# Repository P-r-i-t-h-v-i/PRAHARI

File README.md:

# PRAHARI

Wearable health/safety monitoring band built on Seeed XIAO nRF52840, with LoRa (SX1278/Ra-02/HW-691), MAX30100 heart rate sensor, and MLX90614/AHT20 temperature sensing.

## Hardware

### SX1278 / Ra-02 / HW-691 LoRa Module → XIAO nRF52840
- VCC: 3V3
- GND: GND
- MOSI: D10
- MISO: D9
- SCK: D8
- NSS (CS): D3
- RESET (RST): D2
- DIO0: D1

### MAX30100 Heart Rate Sensor → XIAO nRF52840
- VIN: 3V3
- GND: GND
- SCL: D5
- SDA: D4
- INT: D0 (optional)

### MLX90614 / AHT20 Temperature Sensor(s) → XIAO nRF52840
- VIN/VCC: 3V3
- GND: GND
- SCL: D5
- SDA: D4

### SSD1306 OLED Display → XIAO nRF52840
- VCC: 3V3
- GND: GND
- SDA: D4 (shared I2C bus)
- SCL: D5 (shared I2C bus)

### Shared pins
- **3V3**: shared power rail for all modules. XIAO nRF52840 is not 5V tolerant — do not use a 5V rail.
- **GND**: common star ground for all modules to reduce PPG signal noise.
- **D4 (SDA) / D5 (SCL)**: shared I2C bus. MAX30100, MLX90614, AHT20, and the OLED can all coexist here since each uses a distinct I2C address.

## Structure
- `firmware/oled_test/` — standalone SSD1306 OLED test sketch (Adafruit_GFX + Adafruit_SSD1306)
- `firmware/max30100_test/` — heart rate/SpO2 test sketch (SparkFun MAX3010x library)
- `firmware/i2c_scanner/` — I2C bus scanner, useful for diagnosing wiring/address issues
- `firmware/max30100_probe/` — raw I2C register probe that reads the sensor's PART_ID (0xFF) to identify the actual chip
- `firmware/lora_test/` — SX1278 LoRa test sketch (LoRa library by Sandeep Mistry), currently unresolved: chip not responding over SPI (see Known issues)
- `firmware/lora_probe/` — raw SPI register probe that reads the SX1278's RegVersion (0x42) directly, bypassing the LoRa library
- `firmware/heart_rate_oled/` — combined sketch: reads live heart rate and displays BPM on the SSD1306 OLED
- `pcb/` — KiCad PCB project for the PRAHARI board (schematic, layout, footprints, gerbers, BOM in `pcb/out/`)

## Known hardware note
The "MAX30100" heart-rate breakout in this build actually reports PART_ID `0x15` (MAX30102/MAX30105), not the true MAX30100 (`0x11`) — a common mislabeling on cheap breakout boards. Confirmed via `firmware/max30100_probe`. As a result, `firmware/max30100_test` uses the **SparkFun MAX3010x Pulse and Proximity Sensor Library** (MAX30105 API), not `MAX30100lib`, which fails to initialize against this chip regardless of I2C clock speed.

## Known issues
- LoRa module (SX1278/Ra-02/HW-691) not responding over SPI: `RegVersion` (0x42) reads `0x00` regardless of SPI clock speed (tried 1MHz and 100kHz), and after multiple wiring re-checks (VCC, MISO, GND, MOSI, SCK, NSS, RESET). Frequency (433MHz) and pin mapping have been verified correct in code/source. Suspect either a persistent physical connection fault or a dead module — next step is a multimeter continuity check per-wire, or swapping in a spare module if available.

## Recent changes
- **2026-08-30** — Added standalone SSD1306 OLED test sketch (`firmware/oled_test/oled_test.ino`); flashed and verified on XIAO nRF52840 hardware.
- **2026-08-30** — Added standalone MAX30100 heart rate/SpO2 test sketch (`firmware/max30100_test/max30100_test.ino`); flashed and verified on XIAO nRF52840 hardware.
- **2026-08-30** — Added `firmware/i2c_scanner` and `firmware/max30100_probe` diagnostics; discovered the heart-rate breakout is actually a MAX30102/MAX30105 (PART_ID 0x15) mislabeled as MAX30100; switched `max30100_test` to the SparkFun MAX3010x library, confirmed working (live IR readings on hardware).
- **2026-08-30** — Verified `max30100_test` end-to-end with a live finger on the sensor: IR rose from ~400 (no finger) to ~96000, avg BPM stabilized at 78.
- **2026-08-30** — Added `firmware/lora_test` and `firmware/lora_probe`; LoRa module not yet responding over SPI, diagnosis in progress (see Known issues).
- **2026-08-30** — Added `firmware/heart_rate_oled`, combining the heart-rate sensor with the SSD1306 OLED to display live BPM; flashed and both devices initialized successfully.
- **2026-08-30** — Fixed `heart_rate_oled` showing unrealistically low BPM (e.g. 8) right after placing a finger: the rolling average was dividing by the fixed window size (4) even before 4 real beats were recorded, diluting early readings with zero-initialized buffer slots. Now averages only over beats actually recorded, and resets the average when the finger is removed so a fresh placement doesn't inherit a stale reading.
- **2026-08-30** — Added serial debug logging to `heart_rate_oled` (beat delta/BPM, rejection reason, IR/finger/avg snapshot every 1s); compiled and uploaded to XIAO nRF52840 hardware via arduino-cli (installed `adafruit-nrfutil` locally to enable DFU upload over `/dev/ttyACM0`).
- **2026-09-01** — Added `pcb/` — KiCad PCB project for the PRAHARI board (schematic, layout, footprints, gerbers, BOM).
- **2026-09-01** — Documented repo/Obsidian sync policy in CLAUDE.md: this folder always pushes to `P-r-i-t-h-v-i/PRAHARI` and syncs `Projects/PRAHARI.md` in Obsidian automatically on every change, no confirmation needed.
- **2026-09-02** — Imported rev B PCB from `PRAHARI-PCB.zip` into `pcb/` (replacing rev A files; leftover rev A gerbers/drills in `pcb/out/` root are untracked and pending removal); verified all 38 footprints match schematic, netlist and KiCad 10 libraries pad-for-pad; ran ERC/DRC with kicad-cli 10.0.6 (flatpak): ERC clean (202 known cosmetic warnings), DRC fails the project bar — 3 errors (J6/U2 courtyard collision, RF clearance) + 4 unconnected (LORA_DIO1, DW_VDD ×2, F/B GND pour tie) vs expected 0/0/8; last DRC-clean board is the nested `PRAHARI-revB-verified-20260902-1120.zip`; added `.gitignore` for nested zips, backups and lock files.
- **2026-09-25** — Added `pcb/scripts/build_report_pdf.py` PDF report generator (title/idea, how-it-works, PCB renders, schematic, BOM, build status); iteratively cleaned it to remove PS number/category, the duplicate bottom-PCB image, all "SIH 2026" references (page header and schematic company field), the "open issues" section, and the "things to reconcile" section; added a final "From Prototype to Integrated Board" section answering the prototype-evolution, improvement, and testing-insight/next-steps questions in full prose.
- **2026-09-25** — Removed "rev B hardware" from the PDF report's page footer (was repeated on every page).

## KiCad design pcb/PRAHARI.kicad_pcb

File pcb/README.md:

# PRAHARI — carrier board, rev B

Prototype carrier PCB for **PRAHARI, The Countdown Band** (Point Break, SIH 2026, PS 26181).

**70 × 40 mm, 2 layer, 1.6 mm FR4.** Every active part is still an off-the-shelf
module on a 2.54 mm header. rev B upgrades the sensing, radio and power chain;
the board outline, mounting holes and connector positions are unchanged.

| | |
|---|---|
| Board | 70 × 40 mm, 2 mm corner radius, 4 × M2 mounting holes |
| Stackup | 2 layer, 1.6 mm, 1 oz, GND pour both sides |
| Parts | 38 footprints, 22 BOM line items |
| Routing | 345 tracks / 772 mm, 156 vias (23 routing + 133 ground stitching) |
| Widths | 0.25 mm signal, 0.6 mm power, 0.9 mm RF |
| Pads | 75 SMD, 39 plated through |
| Process | 0.25 mm track / 0.2 mm space / 0.3 mm drill — cheapest JLCPCB & PCBWay tier |
| DRC | **0 violations, 0 unconnected** — 8 cosmetic parity warnings |
| ERC | 202 warnings: 195 off-grid (pre-existing, see *Known warnings*) + 7 deliberate |

---

## What changed from rev A

| | rev A | rev B | Why |
|---|---|---|---|
| PPG | MAX30100 | **MAX30102** | Glass shield, ambient-light cancellation, and 3V3 bus levels — which retires rev A's "1.8 V pull-ups fighting R1/R2" warning entirely |
| Skin temp | MLX90614 (IR) | **MAX30208** (contact) | The thermopile had to see skin across an air gap that wrist curvature keeps changing. A contact digital sensor does not care: ±0.1 °C over I²C |
| Ambient | AHT20 | AHT20 | Unchanged — still the WBGT wet-bulb input |
| Radio | Ra-02 (SX1278) | **Ra-01SH (SX1262)** | 4.2 mA RX vs 11 mA, built-in DC-DC, +22 dBm. **Changes band — see below** |
| Display | 0.96" SSD1306 | **0.91" SSD1306** | Same driver and same 0x3C address, smaller panel, lower peak charge-pump current (<15 mA) |
| Battery | bare LiPo | **DW01A + FS8205A** | On-carrier over-charge / over-discharge / over-current protection |
| Actuator | 1027 ERM + 2N7002 | unchanged | Already correct in rev A |
| MCU | XIAO nRF52840 Sense | unchanged | Already correct in rev A; its BQ25101 is still the only charger |

### ⚠ The radio swap changes the band

The Ra-01SH is an SX1262 part covering **803–930 MHz**. It does *not* cover
433 MHz like the Ra-02 it replaces. Consequences:

- **The whip on J6 drops from 173 mm to 86 mm** (λ/4 at 868 MHz). On a wrist-worn
  band that is a real win — 173 mm of wire was always awkward.
- **In India, keep the radio inside the de-licensed 865–867 MHz sub-band.**
- The deck's "433 MHz mesh" line needs updating to 868 MHz.

If you must stay on 433 MHz, the drop-in is the **Ra-01S / Ra-01SC (SX1268,
410–525 MHz)** — same SPI interface, same BUSY pin, same footprint family. Only
`RA01SH_PINS` and the silkscreen would change. The other option you floated,
the EBYTE E22-400T22S, holds 433 MHz but is a **TTL-UART** module needing
M0/M1/AUX instead of SPI, so it is not a drop-in at all.

---

## What's on it

```
 ANT ▫▫ GND      C3  C1      PRAHARI rev B
 ┌──────────────┐              ┌──────────────────┐
 │  U2 Ra-01SH  │       C2     │ U1  XIAO         │ USB-C
 │  SX1262      │   TP BAT±    │ nRF52840 Sense   │
 │  868 MHz     │   TP 3V3 GND │                  │
 │ U4 C7 R6 U5  │   TP SDA SCL └──────────────────┘
 └──────────────┘
 ┌──────┐ ┌────┐ ┌────┐ ┌────┐            ┌──────┐
 │  J1  │ │ J2 │ │ J3 │ │ J7 │            │  U3  │
 │MAX301│ │MAX │ │AHT │ │OLED│            │ATECC │
 │  02  │ │30208││ 20 │ │0.91│            │ 608A │
 └──────┘ └────┘ └────┘ └────┘            └──────┘
  [J4 BAT]  [J5 MOTOR]  Q1 D1 D2 R3 R4 R5  C4 C5
```

| Ref | Part | Role |
|---|---|---|
| **U1** | Seeed XIAO nRF52840 Sense | MCU, BLE, IMU + mic, BQ25101 LiPo charger |
| **U2** | Ai-Thinker Ra-01SH (SX1262) | LoRa 868 MHz, band-to-band mesh |
| **U3** | ATECC608A-SSHDA (SOIC-8) | Secure element for the anonymised uplink |
| **U4** | DW01A (SOT-23-6) | Li-ion protection: 4.3 V over-charge, 2.4 V over-discharge |
| **U5** | FS8205A (SOT-23-6) | Dual common-drain N-MOSFET — the protection switch pair |
| **J1** | MAX30102 breakout, 1×7 | Red/IR PPG — heart rate, IMU-gated |
| **J2** | MAX30208 breakout, 1×4 | Contact skin temperature, ±0.1 °C |
| **J3** | AHT20 breakout, 1×4 | Air temperature + RH — the WBGT inputs |
| **J7** | 1×4 header | I²C port — 0.91" SSD1306 OLED, or spare |
| **J4** | JST-PH 2 | LiPo in (bare cell — protection is on-board) |
| **J5** | JST-PH 2 | 1027 ERM coin vibration motor |
| **J6** | 2 solder pads | 868 MHz whip + counterpoise |

## GPIO budget

Still exactly 11 GPIO, still all 11 used. The SX1262 has no DIO0 and adds a
**mandatory BUSY**, so D1 changes role and the budget balances unchanged:

| Pin | Net | | Pin | Net |
|---|---|---|---|---|
| D0 | LORA_DIO1 | | D6 | HAPTIC_PWM |
| D1 | **LORA_BUSY** *(was LORA_DIO0)* | | D7 | PPG_INT |
| D2 | LORA_RST | | D8 | SPI_SCK |
| D3 | LORA_NSS | | D9 | SPI_MISO |
| D4 | SDA | | D10 | SPI_MOSI |
| D5 | SCL | | | |

Battery voltage still needs no external divider — the XIAO reads VBAT internally
on P0.31, gated by P0.14, and neither pin reaches the 2×7 header.

A display still costs no GPIO: I²C is a bus, so the SSD1306 hangs off the same
D4/D5 pair as the sensors.

**A Sharp Memory LCD is not possible on this board.** It is an SPI part needing
its own chip-select plus EXTCOMIN, and there is no GPIO left. It only becomes
an option if you move the radio to a UART module and free up SPI.

## I²C bus

| Device | Address |
|---|---|
| AHT20 | 0x38 |
| SSD1306 OLED | 0x3C (0x3D if you move the SA0 jumper) |
| MAX30208 | 0x50 |
| MAX30102 | 0x57 |
| ATECC608A | 0x60 |

Five distinct addresses, no clash. R1/R2 (4k7, on the back) pull up SDA/SCL.
Most breakouts carry their own 4.7 k pull-ups too; with four or five modules
plugged in the bus has plenty, and you can leave R1/R2 unpopulated. Five modules
on flying leads also push bus capacitance toward the 400 pF Fast-mode ceiling —
if the bus is flaky, drop to 100 kHz.

---

## Battery protection (new in rev B)

Standard low-side PCM. The cell's **negative** leg runs through two series FETs
before it becomes system ground, which is why J4 pin 2 is no longer GND:

```
cell+ ──► J4.1 ──► VBAT ──► TP1 ──wire──► XIAO BAT+     (and DW01A VCC via R6)
cell- ──► J4.2 ──► BAT_NEG ──► U5 S1 ──[common drain]──► U5 S2 ──► GND
                                DW01A GND on BAT_NEG, CS on GND (pack-)
```

`BAT_NEG` is a separate net and is deliberately kept out of the ground pour.
`GND` on this board means *pack negative* — the drain side of the FET pair.

### Pin mappings used

| Part | Mapping | Source |
|---|---|---|
| DW01A | 1=OD 2=CS 3=OC 4=TD 5=VCC 6=GND | KiCad's curated `Battery_Management:DW01A` |
| FS8205A | 1=S1 2=G1 3=S2 4=G2 5=D2 6=D1 | KiCad's `Transistor_FET:Q_Dual_NMOS_S1G1S2G2D2D1` |

Note that several secondary web sources give the DW01A as
`1=OC 2=OD 3=CS 4=VSS 5=VDD 6=NC`. That cannot be right — a real DW01A has
*both* VCC and GND plus a TD test pin — so the KiCad mapping is what the board
and the schematic are both built against. Worth one datasheet glance anyway.

### This is redundant with a protected cell

Most 3.7 V 350 mAh wearable cells ship with a DW01A + 8205A PCM already welded
to the tab. Two protections in series is harmless — about 50 mΩ total — but it
is redundant. It is on the carrier because bare cells are rev B's stated
assumption. If you source protected packs, leave U4, U5, R6 and C7 unpopulated
and fit a wire link from J4.2 to the nearest GND pad.

### Charge rate

The 0.5C = 175 mA figure needs checking against the XIAO, not against this
board. The XIAO's on-module BQ25101 sets its charge current with an on-module
resistor and ships configured well below 175 mA. Getting 175 mA means changing
that resistor on the module — the carrier has no charger and cannot influence it.

---

## Before you order — four things to check

**1. Verify the Ra-01SH pad map. This is the biggest open risk on the board.**
The SX1262 *signal set* is certain (NSS, SCK, MOSI, MISO, BUSY, DIO1, NRESET,
VCC, GND, ANT). What is provisional is **which castellated pad each signal sits
on**. The map in `RA01SH_PINS` was chosen to put every signal on the same
physical pad the Ra-02 used, so the routing solution carries over and ANT stays
3.5 mm from J6 — but it is not confirmed against a primary mechanical drawing.
Print `out/gerbers/PRAHARI-F_Cu.gbr` at 1:1, seat a real module on it, and check
before you spend money. If it disagrees, correct that one dict and re-run
`gen_footprints.py` then `gen_pcb.py` — nothing else references pad numbers.

**2. Verify the DW01A OD/OC gate assignment.** `OD(1)` drives `G1` (the FET whose
source sits on B−) and `OC(3)` drives `G2`. That is the usual published
arrangement, but swapping them would make over-discharge protection block
charging instead of discharging. It is a two-line change in the `DW_OD`/`DW_OC`
nets in `design.py`.

**3. The mounting holes are still provisional.** Your `Part1.SLDPRT` /
`Part2.SLDPRT` are the newer proprietary SolidWorks format — not OLE2, not ZIP,
no embedded preview — so the enclosure geometry could not be read. The four M2
holes sit at a symmetric 3.5 mm corner inset. Export the enclosure as **STEP or
DXF** and they can be matched exactly.

**4. Re-price the BOM.** Three parts changed and two were added (U4, U5, R6, C7),
so the deck's ₹3,468 parts total and ₹347-per-worker figure are both stale.

---

---

## Risk register

Ranked by what it costs you if it is wrong. Everything marked *open* needs a
human with the physical part or the enclosure; everything else is closed.

| # | Risk | If wrong | State |
|---|---|---|---|
| 1 | **Ra-01SH pad/signal map** | Board is scrap — every SPI and control line lands on the wrong castellation | **Open.** Mitigated as far as it can be without the part: see below |
| 2 | **DW01A OD/OC gate assignment** | Protection blocks charging instead of discharging — the cell can over-discharge | **Open.** Pin *numbering* is confirmed; only which gate each drives is convention |
| 3 | Mounting holes | Board does not fit the enclosure | **Open.** Needs STEP or DXF — the `.SLDPRT` files cannot be read |
| 4 | Reverse cell insertion on J4 | Reverse voltage reaches the XIAO; the DW01A does **not** protect against this | **Open by design.** J4 is silk-marked `+ −`; check crimp order before first power-up |
| 5 | Protection cluster placement | GND pour stops reaching U4's CS pad — DRC catches it | **Closed.** Guarded by `check_design.py` |
| 6 | `BAT_NEG` track width | Overheating on the cell-negative leg | **Closed.** 0.25 mm / 1 oz ≈ 0.9 A vs ~200 mA peak — about 4× margin |
| 7 | Protection redundant with a protected cell | Nothing — two series FET pairs, ~50 mΩ | **Closed.** DNP path documented above |
| 8 | 195 off-grid ERC warnings hiding a real one | A genuine ERC error goes unnoticed | **Closed.** `check_design.py` triages ERC *by category* and fails on anything that is not off-grid or an isolated label |
| 9 | Stale rev A outputs being uploaded to a fab | Wrong board manufactured | **Closed.** Moved to `out/_revA_archive/`; everything in `out/` is regenerated from the current board |
| 10 | 0.5C = 175 mA charge rate | Slower charging than the deck claims | **Closed as not-our-problem.** It is set by a resistor on the XIAO module, not by this carrier |

### On risk 1 — what is and is not verified

Ai-Thinker publish the Ra-01SH only as image-based or CID-font PDFs, so the pad
table could not be read from a primary source. What *is* established:

- **Signal set — confirmed.** VCC, GND, SCK, MISO, MOSI, NSS, NRESET, BUSY, DIO1,
  ANT (plus optional TXEN/RXEN, which this design leaves unconnected).
  `BUSY` is mandatory on the SX1262 and is wired to D1.
- **Body and package — confirmed** from vendor product data: 17.0 × 16.0 × 3.2 mm,
  dual-row stamp-hole SMD, 16 castellated pads — *identical body to the Ra-02*,
  which is why reusing the rev A pad grid is sound.
- **Which pad carries which signal — NOT confirmed.** This is the open item.

Mitigations already in place:

1. The map lives in exactly one dict, `RA01SH_PINS` in `scripts/design.py`.
   Nothing else in the project references pad numbers — the footprint's pin names
   and the netlist are both derived from it, so they cannot disagree.
2. Every signal sits on the same physical pad the Ra-02 used, so a correction is
   a netlist change, not a re-layout, and ANT stays 3.5 mm from J6.
3. **`out/Ra-01SH-checksheet.svg`** is a 1:1 printable verification sheet.

```bash
python scripts/gen_checksheet.py     # writes out/Ra-01SH-checksheet.svg
```

Open it in a browser, print at **100% / "actual size"** (not "fit to page"),
check the 20 mm ruler on the sheet with a caliper, then seat a real Ra-01SH on
the outline and read off whether pad 8 really is NSS. If it disagrees, fix
`RA01SH_PINS` and re-run `gen_footprints.py` then `gen_pcb.py`.

---

## The guard script

`scripts/check_design.py` re-runs every invariant that was established by hand,
so none of them can regress silently:

```bash
python scripts/check_design.py           # design-level checks, fast
python scripts/check_design.py --full    # + DRC, ERC, and a netlist diff
```

It checks, among other things, that no pad is on two nets, that all 11 XIAO GPIO
are assigned and D1 carries `LORA_BUSY`, that all 16 radio pads are mapped, that
ANT is still on pad 15, that the protection chain is wired as a low-side PCM
pin-for-pin, that `BAT_NEG` is *not* on the Power netclass and *is* in the
router's priority list, and that the protection cluster has not drifted from the
placement that pours cleanly.

With `--full` it also asserts DRC 0/0/8, fails on any ERC category other than
off-grid and isolated labels, and diffs the schematic's own exported netlist
against `design.py` — which is what proves the circuit diagram and the board
still describe the same circuit. **Run it before generating any fab output.**

## Antenna — pick one, not both

The Ra-01SH's ANT pad and the IPEX/U.FL connector on the `-P` variant are the
same RF node.

- **J6 whip (default).** Solder **86 mm** of wire (λ/4 at 868 MHz) to the ANT pad
  and, ideally, another 86 mm to the GND pad as a counterpoise. The RF trace from
  the module to J6 is 3.5 mm of 0.9 mm track over solid ground.
- **IPEX pigtail (better).** Use the Ra-01SH-P, fit a U.FL-to-SMA pigtail, leave
  J6 empty. Zero RF trace.

Do not fit both — a second unterminated path is a stub on the antenna port.
No SMA on the carrier: an edge-launch SMA needs its pads on the board outline (a
real copper-to-edge violation), and a vertical SMA would push the RF trace past
10 mm. Two solder pads 3.5 mm away beat both.

---

## Build and verify

Everything is generated from `scripts/design.py` — components, placement and
netlist live in one file, and **both the schematic and the board are built from
it**, so they cannot drift apart.

```bash
KP="$LOCALAPPDATA/Programs/KiCad/10.0/bin/python.exe"
"$KP" scripts/gen_footprints.py   # XIAO + Ra-01SH (+ Ra-02, kept for rollback)
"$KP" scripts/gen_symbols.py      # XIAO, Ra-01SH, Ra-02, DW01A, FS8205A
"$KP" scripts/gen_project.py      # .kicad_pro, lib tables, design rules
"$KP" scripts/gen_sch.py          # schematic
"$KP" scripts/gen_pcb.py          # place, route, pour, stitch
python scripts/gen_checksheet.py  # 1:1 radio pad-map verification sheet
python scripts/check_design.py --full   # guard: invariants + DRC/ERC + netlist diff
```

**`gen_sch.py` is live again in rev B.** rev A had retired it to protect hand
edits made in eeschema, but a diff showed those edits had not changed the
circuit — same refs, wires, labels and net names — so the schematic is
generated from `design.py` once more. That is what keeps board/schematic parity
at 8 cosmetic warnings while the netlist changes underneath.

`scripts/router.py` is a small two-layer maze router (8-way A* on a 0.1 mm grid,
vias costed at 40 grid units so it prefers to stay on one layer) — KiCad ships
no scriptable autorouter.

To re-check:

```bash
CLI="$LOCALAPPDATA/Programs/KiCad/10.0/bin/kicad-cli.exe"
"$CLI" pcb drc --schematic-parity --severity-all --format json -o out/drc.json PRAHARI.kicad_pcb
"$CLI" sch erc --severity-error --severity-warning --format json -o out/erc.json PRAHARI.kicad_sch
```

Expected: DRC **0 violations, 0 unconnected, 8 parity warnings**; ERC **202
warnings** (195 off-grid + 7 isolated pin labels). Anything else is new.

To rebuild the manufacturing outputs — **use these exact flags.** The CLI
defaults differ from what this project ships and will silently change the file
format if you omit them:

```bash
# BOM - the default --fields drops Description and renames the columns
"$CLI" sch export bom -o out/BOM.csv \
  --fields "Reference,Value,Footprint,Description,QUANTITY" \
  --labels "Reference,Value,Footprint,Description,QUANTITY" \
  --group-by "Value,Footprint" PRAHARI.kicad_sch

# gerbers - without --no-protel-ext you get .gtl/.gbl instead of .gbr
"$CLI" pcb export gerbers -o out/gerbers/ --no-protel-ext \
  --layers "F.Cu,B.Cu,F.Mask,B.Mask,F.Paste,B.Paste,F.Silkscreen,B.Silkscreen,Edge.Cuts" \
  PRAHARI.kicad_pcb

# drills - the flag is --excellon-separate-th, not --separate-files
"$CLI" pcb export drill -o out/gerbers/ --format excellon --excellon-separate-th \
  --generate-map --map-format gerberx2 PRAHARI.kicad_pcb

"$CLI" pcb export pos -o out/positions.csv --format csv --units mm --side both PRAHARI.kicad_pcb
"$CLI" pcb render -o out/top.png --side top --width 1600 --height 1000 --quality high --background opaque PRAHARI.kicad_pcb
```

The gerber zip must contain **14 files**, including `PRAHARI-PTH.drl` and
`PRAHARI-NPTH.drl`. A zip with no `.drl` files is unmanufacturable.

## Manufacturing files

Everything a fab needs is in `out/`:

| File | Use |
|---|---|
| `PRAHARI-gerbers.zip` | upload straight to JLCPCB / PCBWay — 14 files |
| `BOM.csv` | 22 line items, test points and mounting holes excluded |
| `positions.csv` | centroid file, both sides |
| `schematic.pdf` | full schematic |
| `PRAHARI.svg` | same schematic, opens in any browser |
| `netlist.net` | schematic netlist — diff it against `design.py` to prove parity |
| `top.png`, `bottom.png` | 3D renders |
| `drc.json`, `erc.json` | the check reports, regenerated after the last board save |
| `Ra-01SH-checksheet.svg` | **print at 1:1** and verify the radio pad map |
| `_revA_archive/` | superseded rev A renders and zips, kept out of the way |

Order settings: **2 layer, 70 × 40 mm, 1.6 mm, 1 oz, HASL or ENIG.** Nothing on
the board needs better than the default process.

## Assembly order

1. U3 (SOIC-8), U4 and U5 (SOT-23-6), then the 0805/1206 passives — smallest first.
2. Q1 (SOT-23), D1 (SOD-123), D2 (0805 LED).
3. R1, R2 on the **back** side.
4. Headers J1, J2, J3, J7, J6; connectors J4, J5.
5. U2 Ra-01SH — hand-solder the castellations, pin-1 dot at the top left.
6. U1 XIAO last, on a 2×7 header or reflowed onto the castellated lands.
7. Two wires: TP1 → XIAO BAT+, TP2 → XIAO BAT−.

Power up with no battery first and check 3V3 at TP5 before fitting the LiPo.
D2 draws ~1.3 mA continuously — leave it unpopulated for battery-life runs.

## Known warnings

**DRC — 8 schematic parity warnings, cosmetic.** `MOTOR_N`, `ANT` and `HAPTIC_G`
are drawn as bare wires with no net labels, so KiCad auto-names them
`Net-(D1-A)`, `Net-(J6-Pin_1)` and `Net-(Q1-G)` in the schematic while
`design.py` names them explicitly on the board. Same copper, different name. To
clear them, add a net label to each of those three wires.

**ERC — 195 `endpoint_off_grid`, pre-existing.** `gen_sch.py` emits symbol
placements and wire stubs at whole-millimetre offsets rather than snapping to the
1.27 mm connection grid. This is **not new in rev B** — running rev A's
`gen_sch.py` produces 174 of the same warnings. rev A's committed schematic
showed only 7 warnings because that file had been round-tripped through eeschema,
which snaps everything to grid on save. Connectivity is unaffected: DRC reports
0 unconnected and parity holds at 8. To clear them, open `PRAHARI.kicad_sch` in
eeschema and save — or snap `PLACE`, the `ACT` offsets and `WIRES` in
`gen_sch.py` to 1.27 mm multiples.

**ERC — 7 `isolated_pin_label`, all intentional.** `VUSB`, `LORA_DIO2`,
`LORA_DIO3`, `LORA_NC1`, `LORA_NC2`, `PPG_IRD`, `PPG_RD`. These are pins brought
out and named but not used, so the pads carry a meaningful net name if you want
to wire them later. `LORA_NC1`/`NC2` are the two pads the SX1278 used for
DIO4/DIO5 that the SX1262 does not populate.

**One unresolved reference designator.** `gen_pcb.py` reports
`24 placed clear, 1 unresolved` — one silkscreen ref in the crowded U4/C7/R6/U5
cluster could not be auto-placed without overlap. Cosmetic; nudge it in pcbnew if
it bothers you.

## A note on the protection cluster placement

The positions and rotations of U4, U5, R6 and C7 in `design.py` are
**load-bearing**. U4 pin 2 (CS) is the middle pad of a SOT-23-6 and both its
neighbours carry tracks off the part, so the ground pour can only reach CS
head-on. Nudging U4 or rotating it closes that wedge and DRC comes back with
`Missing connection: Zone [GND] on F.Cu ↔ Pad 2 [GND] of U4`. Crowding the pocket
further also breaks the F.Cu-to-B.Cu pour tie. This combination was found by
sweeping placements against DRC — if you move any of the four, re-run
`gen_pcb.py` and confirm `unconnected` is still 0.

`BAT_NEG` is also on the `Default` 0.25 mm netclass rather than `Power`, on
purpose: a 0.6 mm track physically cannot reach a SOT-23-6 pad through a 0.35 mm
inter-pad gap, and the router reported `FAILED: ['BAT_NEG->pad2']` while it was
in `Power`. 0.25 mm on 1 oz carries about 0.9 A against a 175 mA charge current.
It is also in the router's `priority` list, because sorting by span would
otherwise route it last, after the short local nets had boxed in those pads.

## Layout

```
PRAHARI-PCB/
├── PRAHARI.kicad_pro / .kicad_sch / .kicad_pcb / .kicad_sym
├── PRAHARI.pretty/          XIAO, Ra-01SH, Ra-02 footprints
├── fp-lib-table, sym-lib-table
├── scripts/                 design.py, router.py, gen_*.py
└── out/                     gerbers, BOM, positions, PDFs, renders, reports
```

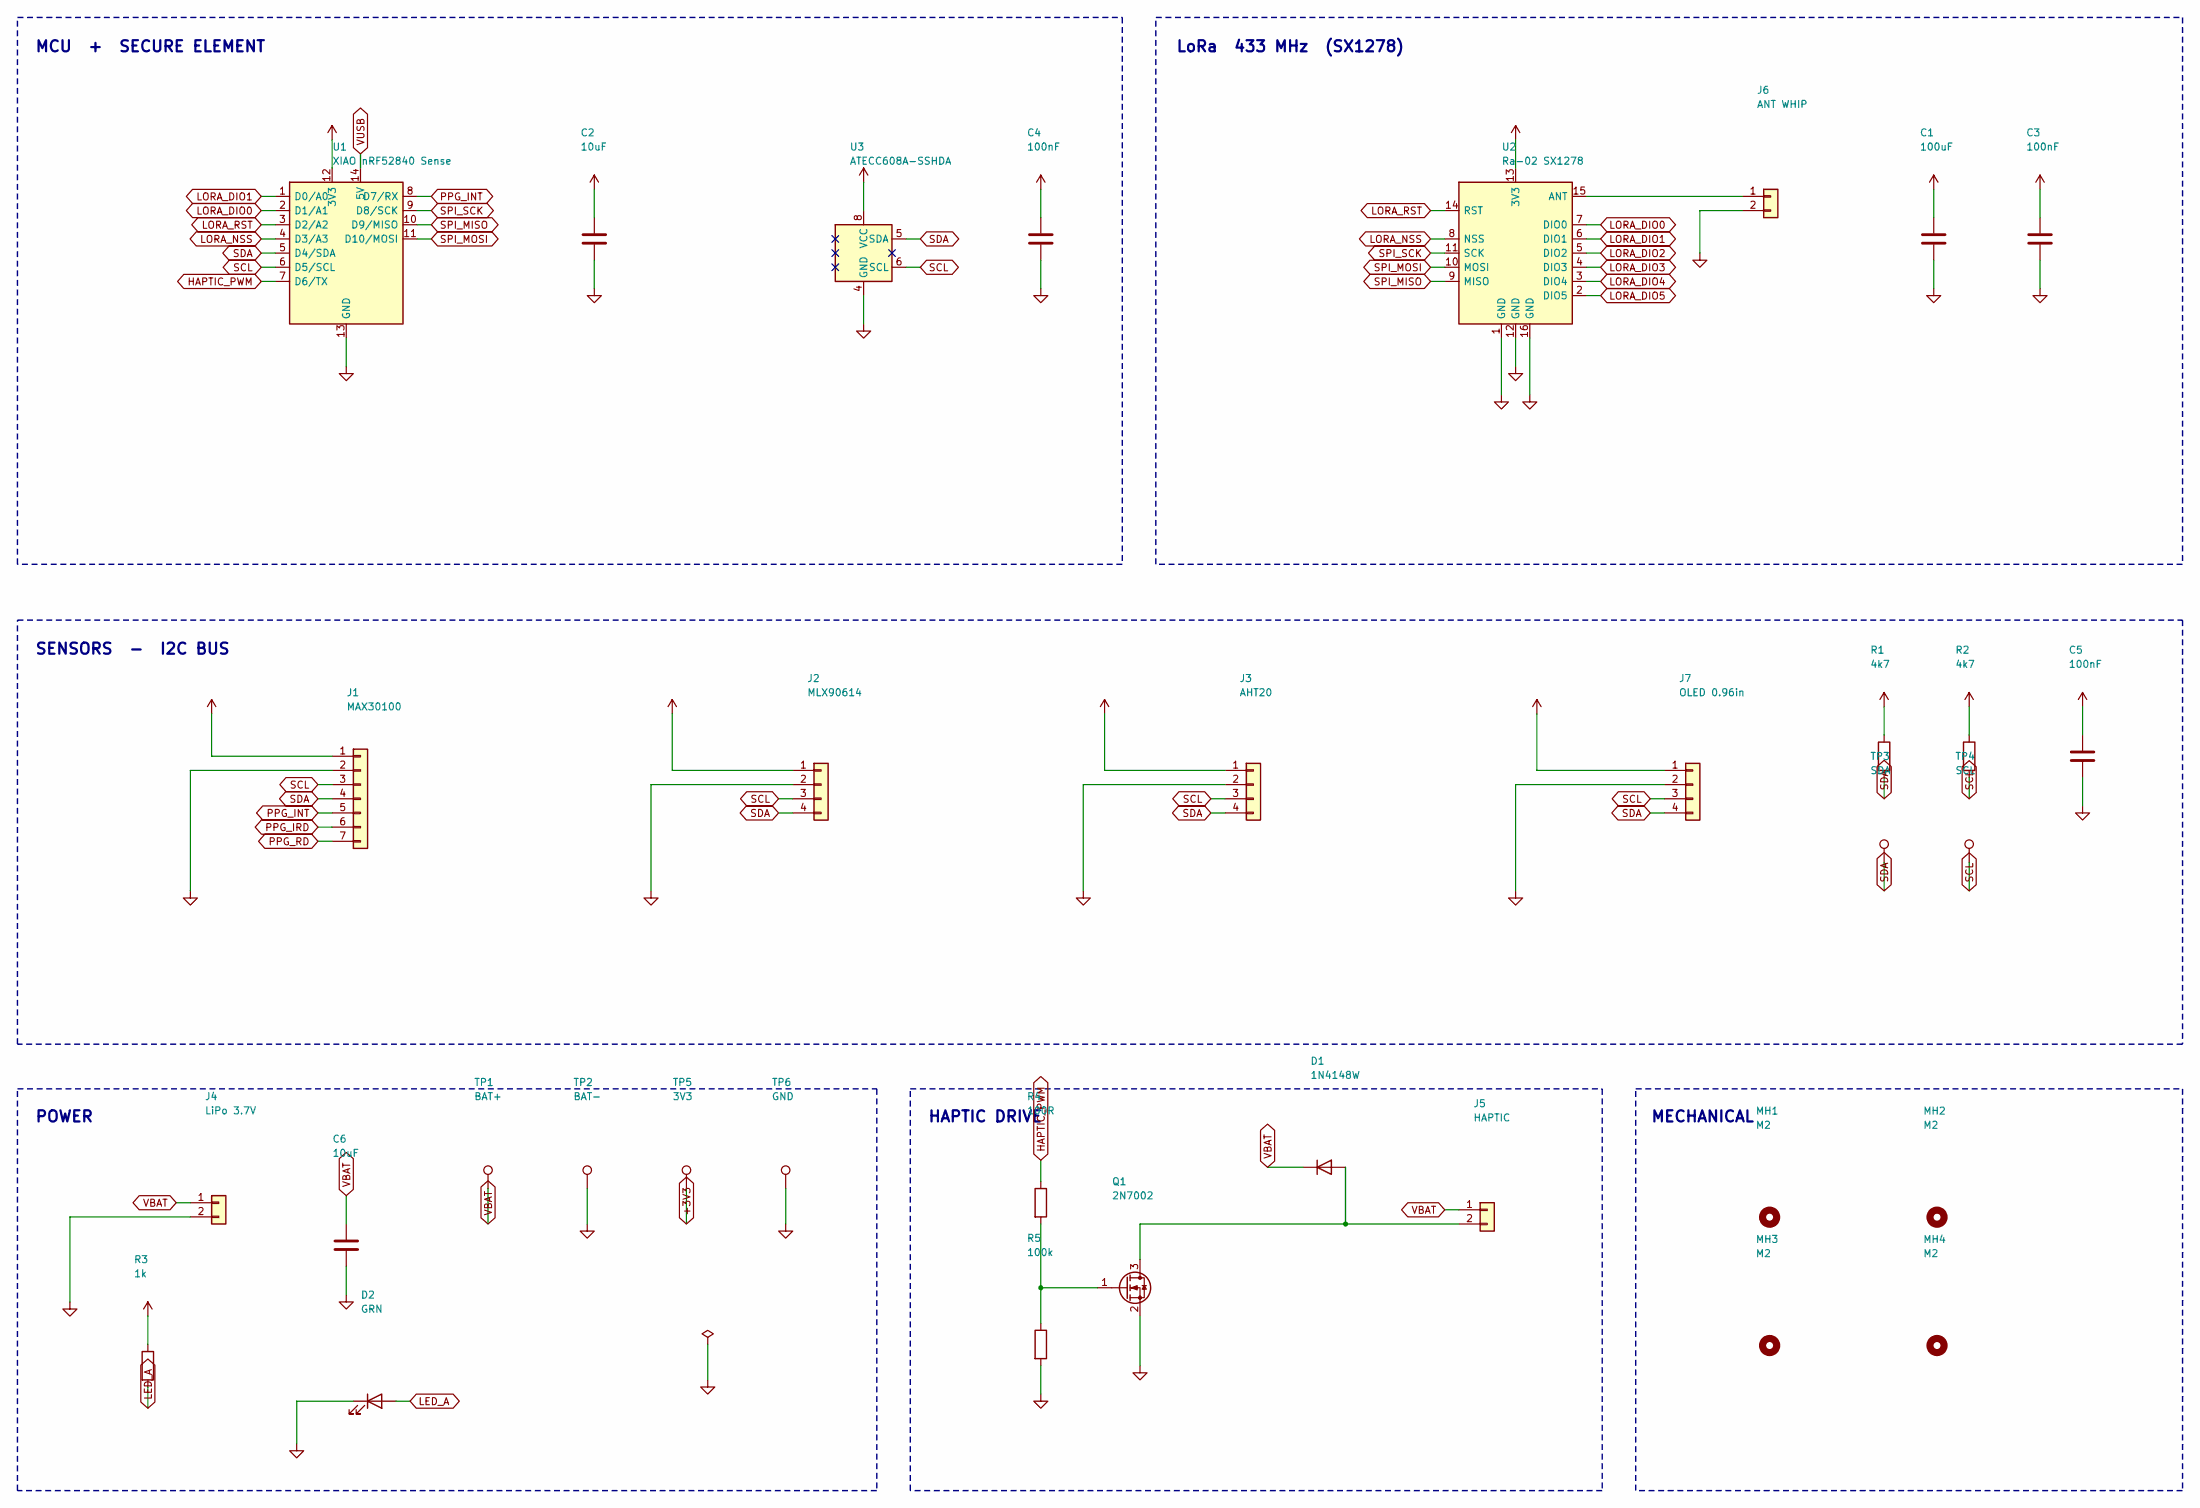
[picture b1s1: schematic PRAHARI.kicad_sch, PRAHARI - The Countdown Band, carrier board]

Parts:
C1: 100uF; C_1206_3216Metric
C2, C6: 10uF; C_0805_2012Metric
C3, C4, C5: 100nF; C_0805_2012Metric
D1: 1N4148W; D_SOD-123
D2: GRN; LED_0805_2012Metric
J1: MAX30100; PinHeader_1x07_P2.54mm_Vertical
J2: MLX90614; PinHeader_1x04_P2.54mm_Vertical
J3: AHT20; PinHeader_1x04_P2.54mm_Vertical
J4: LiPo 3.7V; JST_PH_S2B-PH-K_1x02_P2.00mm_Horizontal
J5: HAPTIC; JST_PH_S2B-PH-K_1x02_P2.00mm_Horizontal
J6: ANT WHIP; PinHeader_1x02_P2.54mm_Vertical
J7: OLED 0.96in; PinHeader_1x04_P2.54mm_Vertical
MH1, MH2, MH3, MH4: M2; MountingHole_2.2mm_M2
Q1: 2N7002; SOT-23
R1, R2: 4k7; R_0805_2012Metric
R3: 1k; R_0805_2012Metric
R4: 100R; R_0805_2012Metric
R5: 100k; R_0805_2012Metric
TP1: BAT+; TestPoint_Pad_D2.0mm
TP2: BAT-; TestPoint_Pad_D2.0mm
TP3: SDA; TestPoint_Pad_D2.0mm
TP4: SCL; TestPoint_Pad_D2.0mm
TP5: 3V3; TestPoint_Pad_D2.0mm
TP6: GND; TestPoint_Pad_D2.0mm
U1: XIAO nRF52840 Sense; XIAO_nRF52840_Sense
U2: Ra-02 SX1278; Ai-Thinker_Ra-02
U3: ATECC608A-SSHDA; SOIC-8_3.9x4.9mm_P1.27mm

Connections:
+3V3: C1.1, C2.1, C3.1, C4.1, C5.1, J1.1, J2.1, J3.1, J7.1, R1.1, R2.1, R3.1, TP5.1, U1.12 (3V3), U2.13 (3V3), U3.8 (VCC)
ANT: J6.1, U2.15 (ANT)
GND: C1.2, C2.2, C3.2, C4.2, C5.2, C6.2, D2.1 (K), J1.2, J2.2, J3.2, J4.2, J6.2, J7.2, Q1.2 (S), R5.2, TP2.1, TP6.1, U1.13 (GND), U2.1 (GND), U2.12 (GND), U2.16 (GND), U3.4 (GND)
HAPTIC_G: Q1.1 (G), R4.2, R5.1
HAPTIC_PWM: R4.1, U1.7 (D6/TX)
LED_A: D2.2 (A), R3.2
LORA_DIO0: U1.2 (D1/A1), U2.7 (DIO0)
LORA_DIO1: U1.1 (D0/A0), U2.6 (DIO1)
LORA_DIO2: U2.5 (DIO2)
LORA_DIO3: U2.4 (DIO3)
LORA_DIO4: U2.3 (DIO4)
LORA_DIO5: U2.2 (DIO5)
LORA_NSS: U1.4 (D3/A3), U2.8 (NSS)
LORA_RST: U1.3 (D2/A2), U2.14 (RST)
MOTOR_N: D1.2 (A), J5.2, Q1.3 (D)
PPG_INT: J1.5, U1.8 (D7/RX)
PPG_IRD: J1.6
PPG_RD: J1.7
SCL: J1.3, J2.3, J3.3, J7.3, R2.2, TP4.1, U1.6 (D5/SCL), U3.6 (SCL)
SDA: J1.4, J2.4, J3.4, J7.4, R1.2, TP3.1, U1.5 (D4/SDA), U3.5 (SDA)
SPI_MISO: U1.10 (D9/MISO), U2.9 (MISO)
SPI_MOSI: U1.11 (D10/MOSI), U2.10 (MOSI)
SPI_SCK: U1.9 (D8/SCK), U2.11 (SCK)
VBAT: C6.1, D1.1 (K), J4.1, J5.1, TP1.1
VUSB: U1.14 (5V)

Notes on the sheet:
HAPTIC DRIVE
LoRa 433 MHz (SX1278)
MECHANICAL
SENSORS - I2C BUS
MCU + SECURE ELEMENT
POWER

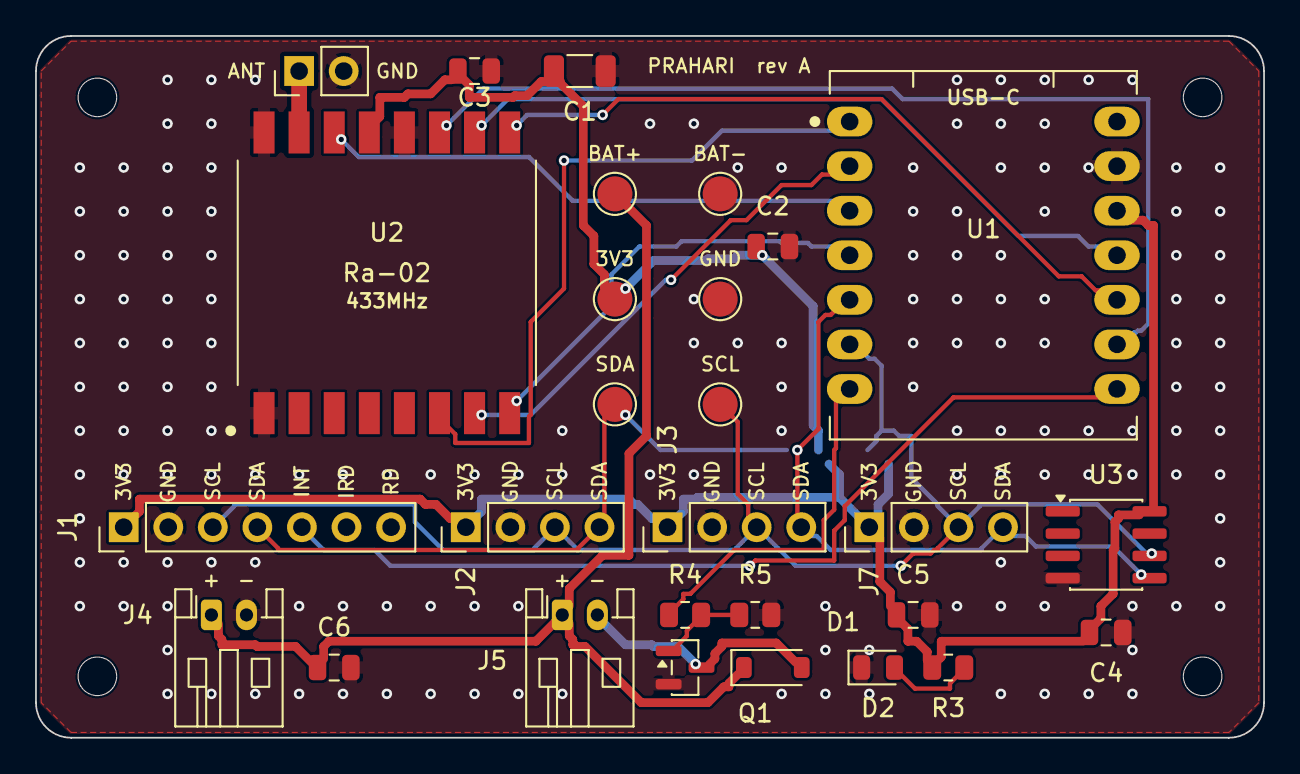
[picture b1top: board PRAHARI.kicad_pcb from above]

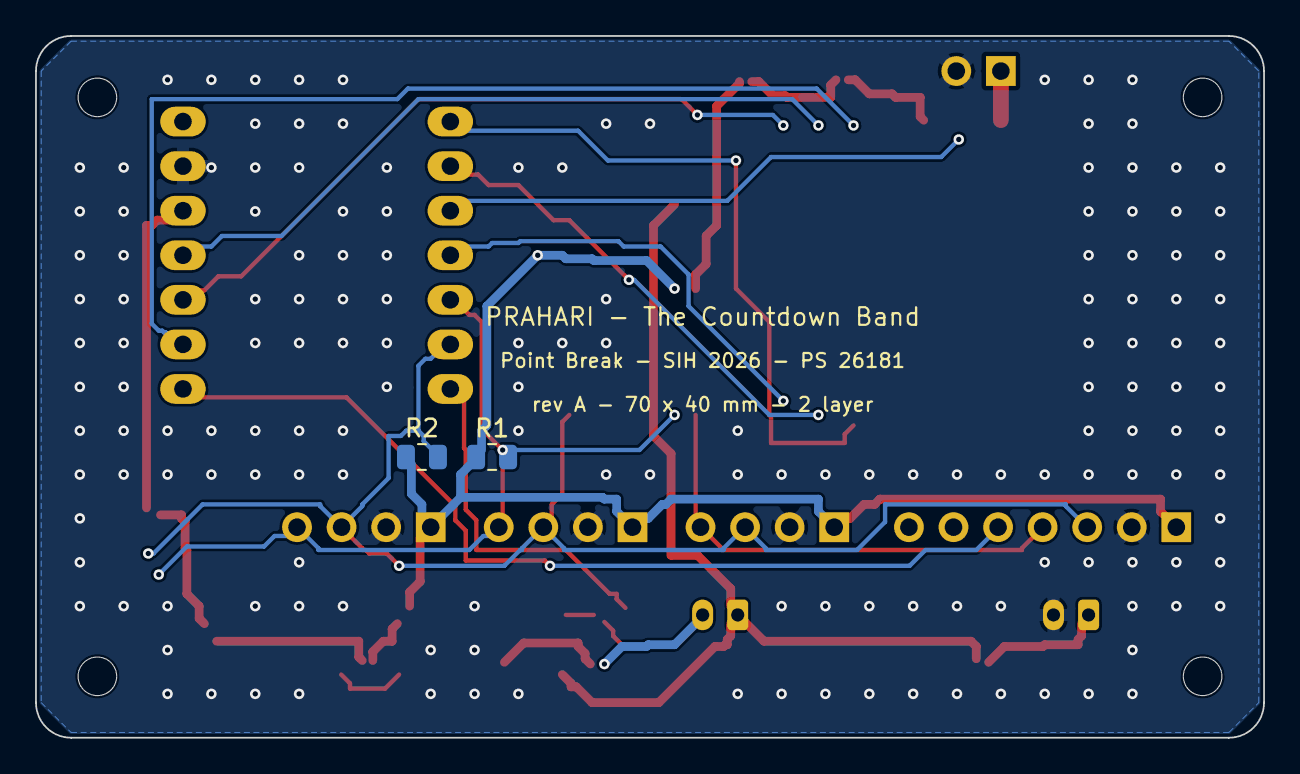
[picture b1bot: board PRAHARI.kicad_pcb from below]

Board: 2 copper layers, 70.0 x 40.0 mm, 34 parts (2 on the bottom side), 18 nets.

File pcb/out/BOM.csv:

"Reference","Value","Footprint","Description","QUANTITY"
"C1","100uF","Capacitor_SMD:C_1206_3216Metric","LoRa TX bulk (118 mA at +22 dBm)","1"
"C2,C6","10uF","Capacitor_SMD:C_0805_2012Metric","3V3 bulk at the XIAO,VBAT bulk","2"
"C3-C5,C7","100nF","Capacitor_SMD:C_0805_2012Metric","ATECC608A decoupling,DW01A VDD decoupling,Ra-01SH decoupling,Sensor rail decoupling","4"
"D1","1N4148W","Diode_SMD:D_SOD-123","Motor flyback clamp","1"
"D2","GRN","LED_SMD:LED_0805_2012Metric","3V3 power LED","1"
"J1","MAX30102","Connector_PinHeader_2.54mm:PinHeader_1x07_P2.54mm_Vertical","Red/IR PPG - heart rate, IMU-gated","1"
"J2","MAX30208","Connector_PinHeader_2.54mm:PinHeader_1x04_P2.54mm_Vertical","Contact skin temperature - +/-0.1 C clinical, I2C 0x50","1"
"J3","AHT20","Connector_PinHeader_2.54mm:PinHeader_1x04_P2.54mm_Vertical","Air temperature + RH - the WBGT inputs","1"
"J4","LiPo 3.7V 350mAh","Connector_JST:JST_PH_S2B-PH-K_1x02_P2.00mm_Horizontal","Bare cell in - protected by U4/U5, then to XIAO BAT pads via TP1/TP2","1"
"J5","HAPTIC","Connector_JST:JST_PH_S2B-PH-K_1x02_P2.00mm_Horizontal","1027 ERM coin motor - hazard and strain patterns","1"
"J6","ANT WHIP","Connector_PinHeader_2.54mm:PinHeader_1x02_P2.54mm_Vertical","868 MHz whip (86 mm) / counterpoise solder pads","1"
"J7","OLED 0.91in","Connector_PinHeader_2.54mm:PinHeader_1x04_P2.54mm_Vertical","0.91in SSD1306 128x32 I2C OLED at 0x3C - countdown display","1"
"Q1","2N7002","Package_TO_SOT_SMD:SOT-23","Haptic low-side switch","1"
"R1,R2","4k7","Resistor_SMD:R_0805_2012Metric","SCL pull-up,SDA pull-up","2"
"R3","1k","Resistor_SMD:R_0805_2012Metric","LED series","1"
"R4,R6","100R","Resistor_SMD:R_0805_2012Metric","DW01A VDD series,Gate series","2"
"R5","100k","Resistor_SMD:R_0805_2012Metric","Gate pull-down","1"
"U1","XIAO nRF52840 Sense","PRAHARI:XIAO_nRF52840_Sense","MCU: Cortex-M4F, BLE, on-board IMU + mic + BQ25101 LiPo charger","1"
"U2","Ra-01SH SX1262","PRAHARI:Ai-Thinker_Ra-01SH","LoRa SX1262 868/915 MHz, band-to-band mesh, 4.2 mA RX","1"
"U3","ATECC608A-SSHDA","Package_SO:SOIC-8_3.9x4.9mm_P1.27mm","Secure element: key storage for the anonymised uplink","1"
"U4","DW01A","Package_TO_SOT_SMD:SOT-23-6","Li-ion protection: 4.3 V over-charge, 2.4 V over-discharge, over-current","1"
"U5","FS8205A","Package_TO_SOT_SMD:SOT-23-6","Dual common-drain N-MOSFET - the protection switch pair","1"
